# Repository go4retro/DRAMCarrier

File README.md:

# DRAMCarrier

Convert an 8-4164 DRAM based Commodore to utilize 2 4464 DRAMs or an SRAM replacement system

## Options

Contrary to first glance, C64 motherboard models 250407 and 250425 do __NOT__ share the same 8 DRAM IC layout.  It's close, but just slightly off.  Therefore, there are two versions of this carrier design, one for each motherboard. 

There's no logic on the PCB, it just passively maps the 8 individual IO signals from each DRAM socket to one of the 2 4464 DRAM footprints.  Care has been taken to preserve the relative order, so D0 on the 4164 and D0 on the 4464 should be the same.

I designed this board to allow use of the new 2 Megabyte SRAM replacement 9which natively fits in 2 DRAM-IC motherboards, without having to create a brand new design.  This design is also useful to simply replace the 8 original 4164s with 2 4464 ICs, or a simple 64kB SRAM RAM replacement

I am considering creating a run of these designs.  Let me know if there is interest.

## License
Copyright (C) 2018  RETRO Innovations

These files are free designs; you can redistribute them and/or modify
them under the terms of the Creative Commons Attribution-ShareAlike 
4.0 International License.

You should have received a copy of the license along with this
work. If not, see <http://creativecommons.org/licenses/by-sa/4.0/>.

These files are distributed in the hope that they will be useful,
but WITHOUT ANY WARRANTY; without even the implied warranty of
MERCHANTABILITY or FITNESS FOR A PARTICULAR PURPOSE.  See the
license for more details.

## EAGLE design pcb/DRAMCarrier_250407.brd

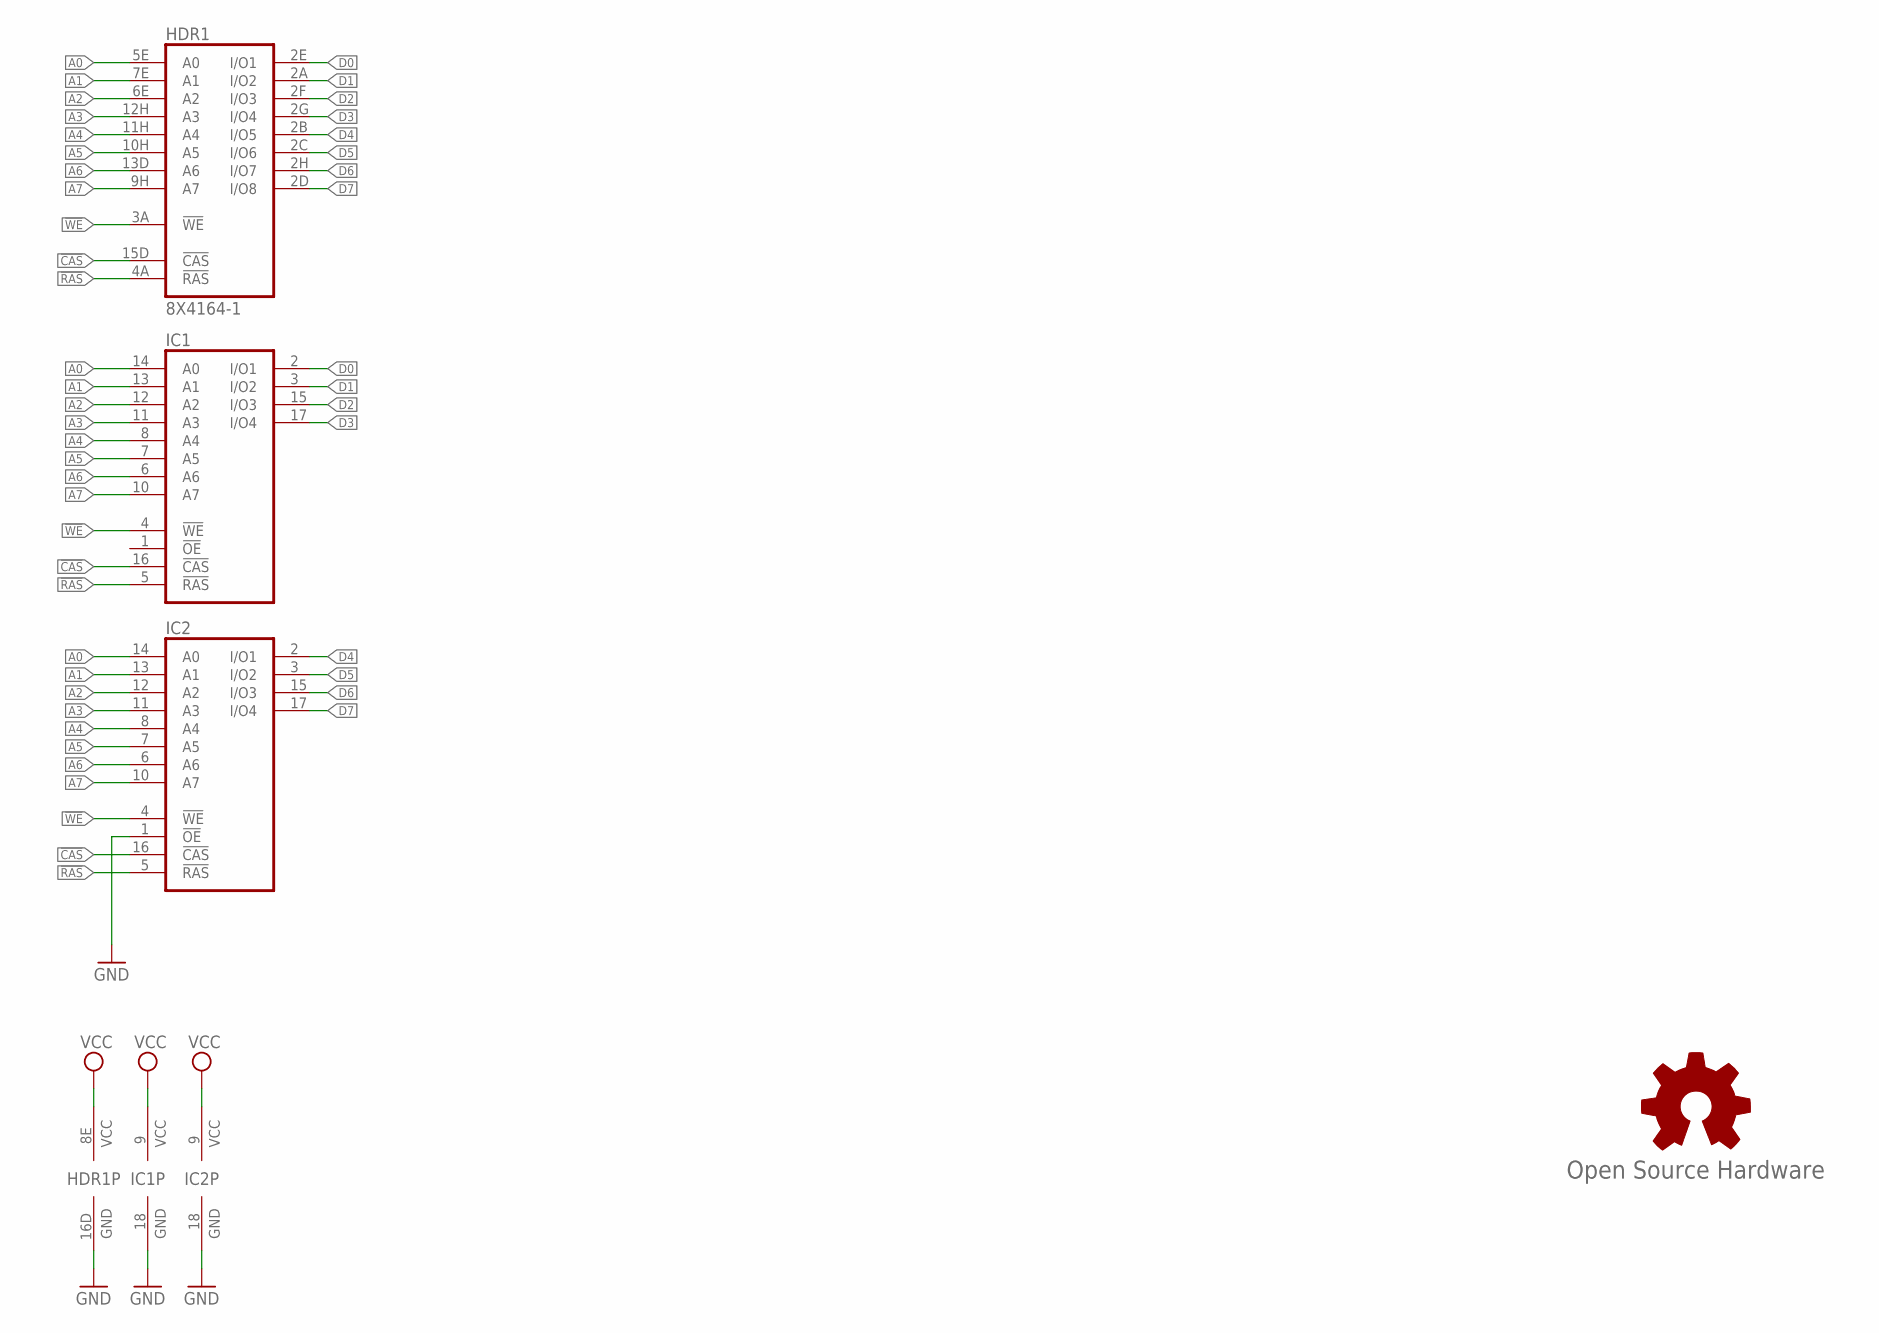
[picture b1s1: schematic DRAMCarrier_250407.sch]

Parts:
GOLD_ORB_SM1: Open Source Hardware; OSHW_8MM
HDR1: 8X4164-1; 8XDIL16_REV
IC1, IC2: 41464C; DIL18

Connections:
!CAS: HDR1.15D (!CAS), IC1.16 (!CAS), IC2.16 (!CAS)
!RAS: HDR1.4A (!RAS), IC1.5 (!RAS), IC2.5 (!RAS)
!WE: HDR1.3A (!WE), IC1.4 (!WE), IC2.4 (!WE)
A0: HDR1.5E (A0), IC1.14 (A0), IC2.14 (A0)
A1: HDR1.7E (A1), IC1.13 (A1), IC2.13 (A1)
A2: HDR1.6E (A2), IC1.12 (A2), IC2.12 (A2)
A3: HDR1.12H (A3), IC1.11 (A3), IC2.11 (A3)
A4: HDR1.11H (A4), IC1.8 (A4), IC2.8 (A4)
A5: HDR1.10H (A5), IC1.7 (A5), IC2.7 (A5)
A6: HDR1.13D (A6), IC1.6 (A6), IC2.6 (A6)
A7: HDR1.9H (A7), IC1.10 (A7), IC2.10 (A7)
D0: HDR1.2E (I/O1), IC1.2 (I/O1)
D1: HDR1.2A (I/O2), IC1.3 (I/O2)
D2: HDR1.2F (I/O3), IC1.15 (I/O3)
D3: HDR1.2G (I/O4), IC1.17 (I/O4)
D4: HDR1.2B (I/O5), IC2.2 (I/O1)
D5: HDR1.2C (I/O6), IC2.3 (I/O2)
D6: HDR1.2H (I/O7), IC2.15 (I/O3)
D7: HDR1.2D (I/O8), IC2.17 (I/O4)
GND: HDR1.16D (GND), IC1.18 (GND), IC2.1 (!OE), IC2.18 (GND)
VCC: HDR1.8E (VCC), IC1.9 (VCC), IC2.9 (VCC)

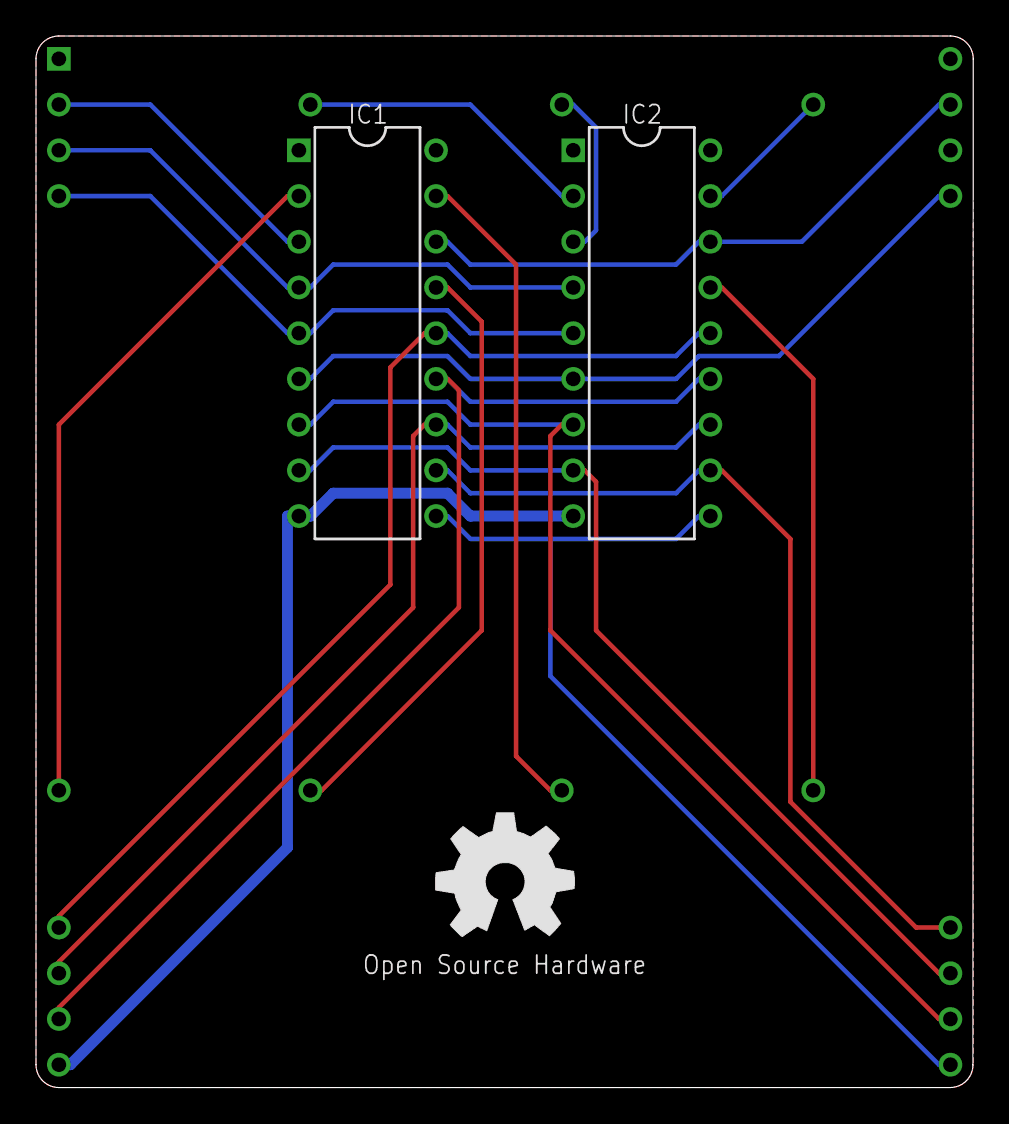
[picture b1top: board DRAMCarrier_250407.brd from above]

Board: 2 copper layers, 52.1 x 58.4 mm, 4 parts (0 on the bottom side), 21 nets.

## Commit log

2020-10-11 Add README.md
2020-10-20 Fixed wrong motherboard number on design and readme

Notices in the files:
pcb/DRAMCarrier_250407.brd:
(c)2019 RETRO Innovations
